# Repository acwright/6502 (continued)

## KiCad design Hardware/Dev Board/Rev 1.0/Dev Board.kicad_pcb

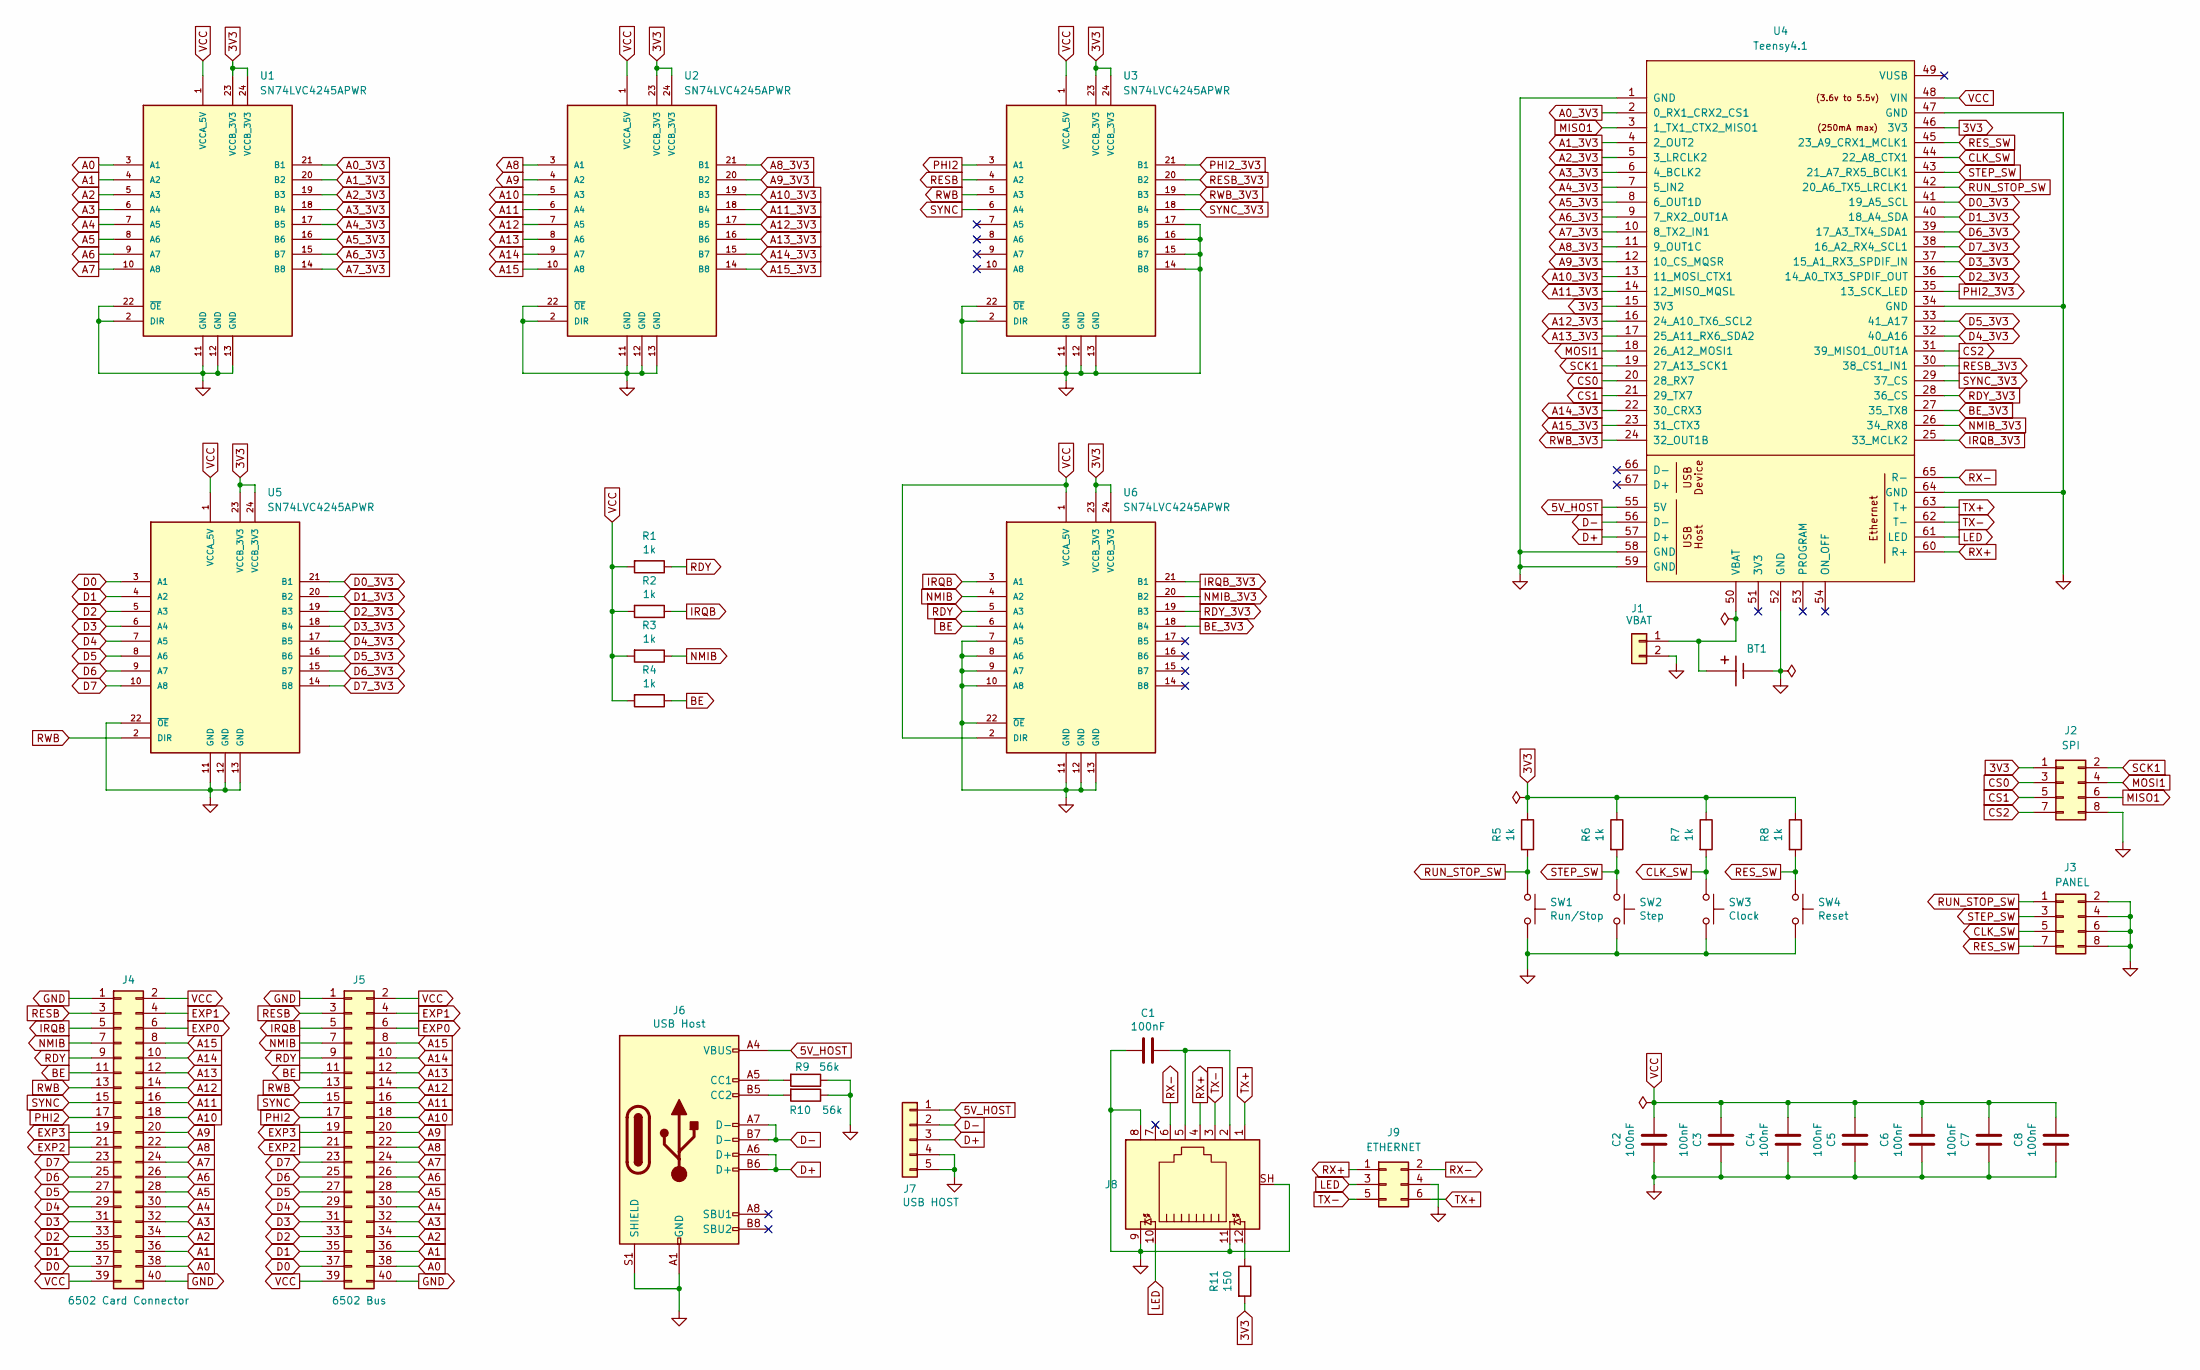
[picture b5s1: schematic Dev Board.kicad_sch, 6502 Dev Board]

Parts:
BT1: BAT-HLD-001-THM; BAT_BAT-HLD-001-THM
C1, C2, C3, C4, C5, C6, C7, C8: 100nF; C_0805_2012Metric; LCSC C49678
J1: VBAT; PinHeader_1x02_P2.54mm_Vertical
J2: SPI; PinHeader_2x04_P2.54mm_Vertical
J3: PANEL; PinHeader_2x04_P2.54mm_Vertical
J4: 6502 Card Connector; RHDR40W82P485X254_2X20_5740X93
J5: 6502 Bus; 6502 Bus Connector
J6: USB Host; USB_C_Receptacle_HRO_TYPE-C-31-M-12; LCSC C2988369
J7: USB HOST; PinHeader_1x05_P2.54mm_Vertical
J8: RJ45_LED; J1B1211CCD; MPN J1B1211CCD
J9: ETHERNET; PinHeader_2x03_P2.00mm_Vertical
R1, R2, R3, R4, R5, R6, R7, R8: 1k; R_0805_2012Metric; LCSC C17513
R9, R10: 56k; R_0805_2012Metric; LCSC C169923
R11: 150; R_0805_2012Metric; LCSC C17471
SW1: Run/Stop; SW_TS-1187A-B-A-B; LCSC C318884
SW2: Step; SW_TS-1187A-B-A-B; LCSC C318884
SW3: Clock; SW_TS-1187A-B-A-B; LCSC C318884
SW4: Reset; SW_TS-1187A-B-A-B; LCSC C318884
U1, U2, U3, U5, U6: SN74LVC4245APWR; TSSOP-24_4.4x7.8mm_P0.65mm; LCSC C7859
U4: Teensy4.1; Teensy41

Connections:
3V3: J2.1, R5.1, R6.1, R7.1, R8.1, R11.2, U1.23 (VCCB_3V3), U1.24 (VCCB_3V3), U2.23 (VCCB_3V3), U2.24 (VCCB_3V3), U3.23 (VCCB_3V3), U3.24 (VCCB_3V3), U4.15 (3V3), U4.46 (3V3), U5.23 (VCCB_3V3), U5.24 (VCCB_3V3), U6.23 (VCCB_3V3), U6.24 (VCCB_3V3)
5V_HOST: J6.A4 (VBUS), J6.A9 (VBUS), J6.B4 (VBUS), J6.B9 (VBUS), J7.1, U4.55 (5V)
A0: J4.38, J5.38, U1.3 (A1)
A0_3V3: U1.21 (B1), U4.2 (0_RX1_CRX2_CS1)
A1: J4.36, J5.36, U1.4 (A2)
A1_3V3: U1.20 (B2), U4.4 (2_OUT2)
A2: J4.34, J5.34, U1.5 (A3)
A2_3V3: U1.19 (B3), U4.5 (3_LRCLK2)
A3: J4.32, J5.32, U1.6 (A4)
A3_3V3: U1.18 (B4), U4.6 (4_BCLK2)
A4: J4.30, J5.30, U1.7 (A5)
A4_3V3: U1.17 (B5), U4.7 (5_IN2)
A5: J4.28, J5.28, U1.8 (A6)
A5_3V3: U1.16 (B6), U4.8 (6_OUT1D)
A6: J4.26, J5.26, U1.9 (A7)
A6_3V3: U1.15 (B7), U4.9 (7_RX2_OUT1A)
A7: J4.24, J5.24, U1.10 (A8)
A7_3V3: U1.14 (B8), U4.10 (8_TX2_IN1)
A8: J4.22, J5.22, U2.3 (A1)
A8_3V3: U2.21 (B1), U4.11 (9_OUT1C)
A9: J4.20, J5.20, U2.4 (A2)
A9_3V3: U2.20 (B2), U4.12 (10_CS_MQSR)
A10: J4.18, J5.18, U2.5 (A3)
A10_3V3: U2.19 (B3), U4.13 (11_MOSI_CTX1)
A11: J4.16, J5.16, U2.6 (A4)
A11_3V3: U2.18 (B4), U4.14 (12_MISO_MQSL)
A12: J4.14, J5.14, U2.7 (A5)
A12_3V3: U2.17 (B5), U4.16 (24_A10_TX6_SCL2)
A13: J4.12, J5.12, U2.8 (A6)
A13_3V3: U2.16 (B6), U4.17 (25_A11_RX6_SDA2)
A14: J4.10, J5.10, U2.9 (A7)
A14_3V3: U2.15 (B7), U4.22 (30_CRX3)
A15: J4.8, J5.8, U2.10 (A8)
A15_3V3: U2.14 (B8), U4.23 (31_CTX3)
BE: J4.11, J5.11, R4.1, U6.6 (A4)
BE_3V3: U4.27 (35_TX8), U6.18 (B4)
CLK_SW: J3.5, R7.2, SW3.1, U4.44 (22_A8_CTX1)
CS0: J2.3, U4.20 (28_RX7)
CS1: J2.5, U4.21 (29_TX7)
CS2: J2.7, U4.31 (39_MISO1_OUT1A)
D0: J4.37, J5.37, U5.3 (A1)
D0_3V3: U4.41 (19_A5_SCL), U5.21 (B1)
D1: J4.35, J5.35, U5.4 (A2)
D1_3V3: U4.40 (18_A4_SDA), U5.20 (B2)
D2: J4.33, J5.33, U5.5 (A3)
D2_3V3: U4.36 (14_A0_TX3_SPDIF_OUT), U5.19 (B3)
D3: J4.31, J5.31, U5.6 (A4)
D3_3V3: U4.37 (15_A1_RX3_SPDIF_IN), U5.18 (B4)
D4: J4.29, J5.29, U5.7 (A5)
D4_3V3: U4.32 (40_A16), U5.17 (B5)
D5: J4.27, J5.27, U5.8 (A6)
D5_3V3: U4.33 (41_A17), U5.16 (B6)
D6: J4.25, J5.25, U5.9 (A7)
D6_3V3: U4.39 (17_A3_TX4_SDA1), U5.15 (B7)
D7: J4.23, J5.23, U5.10 (A8)
D7_3V3: U4.38 (16_A2_RX4_SCL1), U5.14 (B8)
D+: J6.A6 (D+), J6.B6 (D+), J7.3, U4.57 (D+)
D-: J6.A7 (D-), J6.B7 (D-), J7.2, U4.56 (D-)
EXP0: J4.6, J5.6
EXP1: J4.4, J5.4
EXP2: J4.21, J5.21
EXP3: J4.19, J5.19
GND: BT1.-, C1.2, C2.2, C3.1, C4.2, C5.1, C6.2, C7.1, C8.2, J1.2, J2.8, J3.2, J3.4, J3.6, J3.8, J4.1, J4.40, J5.1, J5.40, J6.A1 (GND), J6.A12 (GND), J6.B1 (GND), J6.B12 (GND), J6.S1 (SHIELD), J7.4, J7.5, J8.8, J8.9, J8.11, J8.SH, J9.4, R9.1, R10.1, SW1.2, SW2.2, SW3.2, SW4.2, U1.2 (DIR), U1.11 (GND), U1.12 (GND), U1.13 (GND), U1.22 (~OE), U2.2 (DIR), U2.11 (GND), U2.12 (GND), U2.13 (GND), U2.22 (~OE), U3.2 (DIR), U3.11 (GND), U3.12 (GND), U3.13 (GND), U3.14 (B8), U3.15 (B7), U3.16 (B6), U3.17 (B5), U3.22 (~OE), U4.1 (GND), U4.34 (GND), U4.47 (GND), U4.52 (GND), U4.58 (GND), U4.59 (GND), U4.64 (GND), U5.11 (GND), U5.12 (GND), U5.13 (GND), U5.22 (~OE), U6.7 (A5), U6.8 (A6), U6.9 (A7), U6.10 (A8), U6.11 (GND), U6.12 (GND), U6.13 (GND), U6.22 (~OE)
IRQB: J4.5, J5.5, R2.1, U6.3 (A1)
IRQB_3V3: U4.25 (33_MCLK2), U6.21 (B1)
LED: J8.10, J9.3, U4.61 (LED)
MISO1: J2.6, U4.3 (1_TX1_CTX2_MISO1)
MOSI1: J2.4, U4.18 (26_A12_MOSI1)
NMIB: J4.7, J5.7, R3.1, U6.4 (A2)
NMIB_3V3: U4.26 (34_RX8), U6.20 (B2)
unnamed: C1.1, J8.2, J8.5
unnamed: BT1.+, J1.1, U4.50 (VBAT)
unnamed: J6.A5 (CC1), R9.2
unnamed: J6.B5 (CC2), R10.2
unnamed: J8.12, R11.1
PHI2: J4.17, J5.17, U3.3 (A1)
PHI2_3V3: U3.21 (B1), U4.35 (13_SCK_LED)
RDY: J4.9, J5.9, R1.1, U6.5 (A3)
RDY_3V3: U4.28 (36_CS), U6.19 (B3)
RESB: J4.3, J5.3, U3.4 (A2)
RESB_3V3: U3.20 (B2), U4.30 (38_CS1_IN1)
RES_SW: J3.7, R8.2, SW4.1, U4.45 (23_A9_CRX1_MCLK1)
RUN_STOP_SW: J3.1, R5.2, SW1.1, U4.42 (20_A6_TX5_LRCLK1)
RWB: J4.13, J5.13, U3.5 (A3), U5.2 (DIR)
RWB_3V3: U3.19 (B3), U4.24 (32_OUT1B)
RX+: J8.4, J9.1, U4.60 (R+)
RX-: J8.6, J9.2, U4.65 (R-)
SCK1: J2.2, U4.19 (27_A13_SCK1)
STEP_SW: J3.3, R6.2, SW2.1, U4.43 (21_A7_RX5_BCLK1)
SYNC: J4.15, J5.15, U3.6 (A4)
SYNC_3V3: U3.18 (B4), U4.29 (37_CS)
TX+: J8.1, J9.6, U4.63 (T+)
TX-: J8.3, J9.5, U4.62 (T-)
VCC: C2.1, C3.2, C4.1, C5.2, C6.1, C7.2, C8.1, J4.2, J4.39, J5.2, J5.39, R1.2, R2.2, R3.2, R4.2, U1.1 (VCCA_5V), U2.1 (VCCA_5V), U3.1 (VCCA_5V), U4.48 (VIN), U5.1 (VCCA_5V), U6.1 (VCCA_5V), U6.2 (DIR)

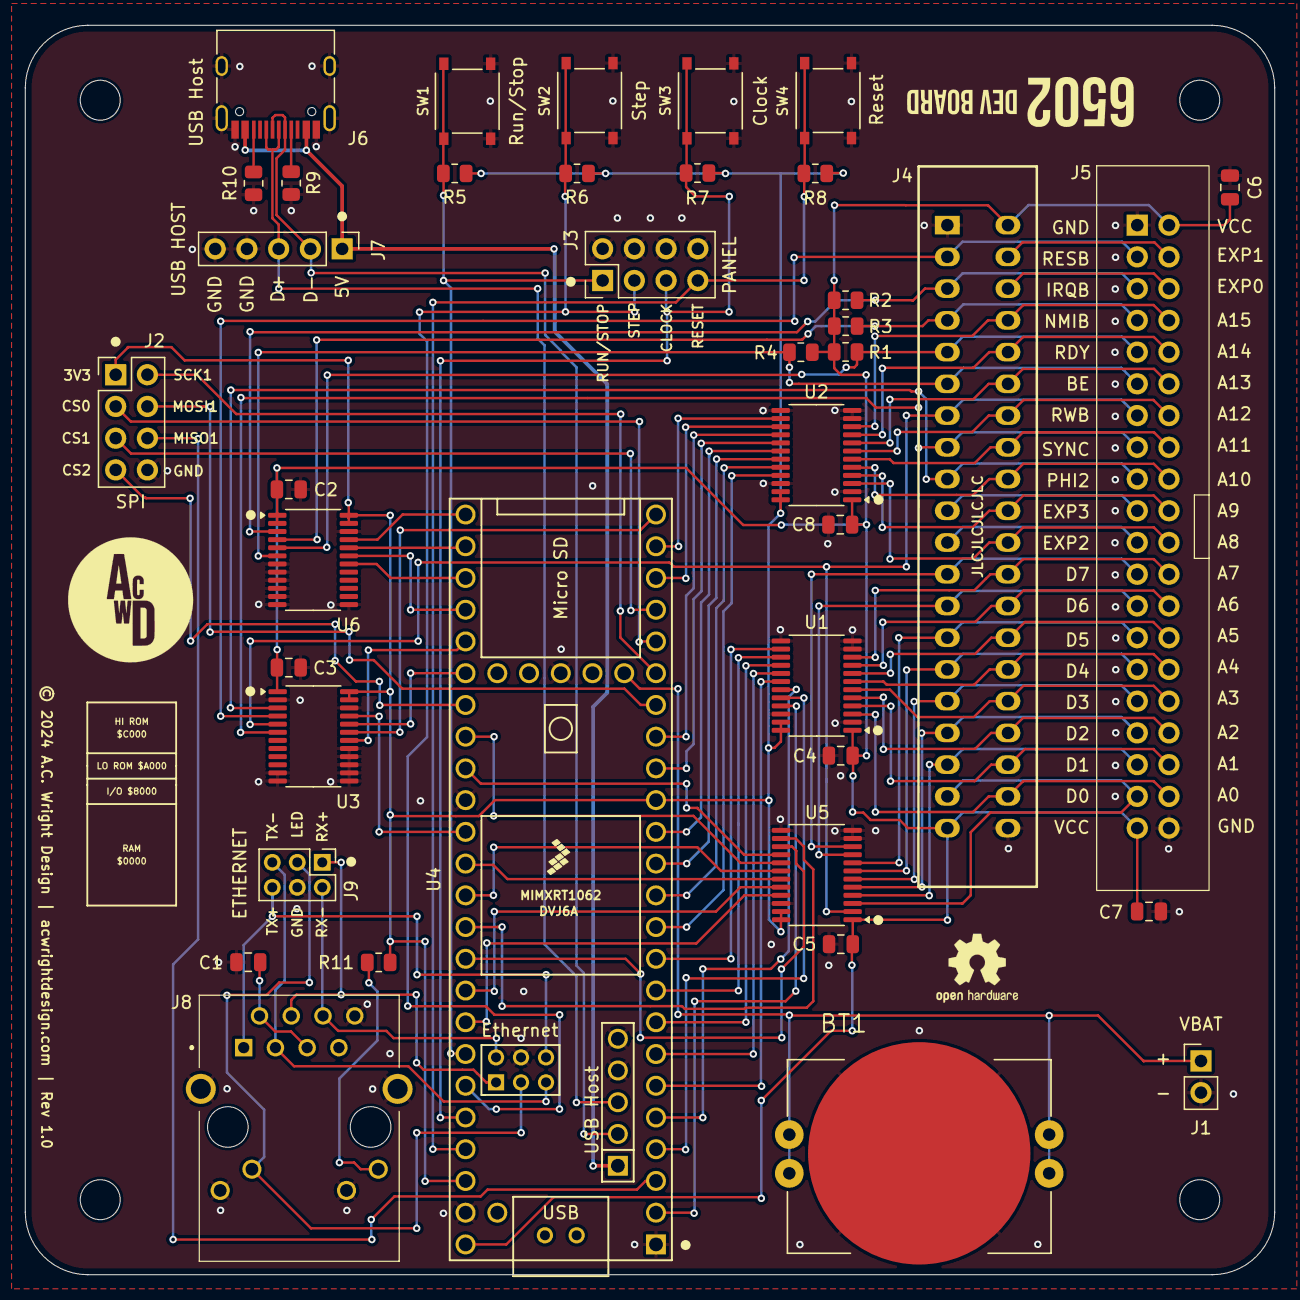
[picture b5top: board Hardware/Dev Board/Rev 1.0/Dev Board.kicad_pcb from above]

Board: 2 copper layers, 100.0 x 100.0 mm, 43 parts (0 on the bottom side), 94 nets.

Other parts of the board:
H1, H2, H3, H4: MountingHole; MountingHole_3.2mm_M3
